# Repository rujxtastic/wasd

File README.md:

# WASD
The four most basic keys for gaming. Forward, Backward, and either Strafe or Look left/right.   
But how often do you ever step back and think, **what am I putting them through**? Your character is in a constant state of running around aimlessly, not knowing their next move. If only you could be in their shoes and empathise with them. That is the real-world problem that WASD solves.   
Realistically, WASD is the problem to the solution. You will find yourself chasing down your keyboard as it edges away from you, inflicting a fraction of your character's pain on you. A little toy that serves no real purpose (like us all?). The Onshape link can be found [here](https://cad.onshape.com/documents/5a513a08f5c3c2de2939b5e3/w/8555595e139211449ba911fa/e/058102c6ac5f3245f4983aa2?renderMode=0&uiState=69daf673cb233122137885a0).

# What does it do?
At the moment it can:
- Type W, A, S, D
- When W is typed, it moves forward via two wheels on the side.
- When S is typed, it moves backwards.
- A and D rotate it (omni wheels were too expensive!).

# Why does it do?
In the keyboard universe, most improvements have already been done long ago. Matrices, LEDs and stenographers have been completed a million times over: so much so that the people are becoming bored and complacent. WASD came to me when I was discussing ideas with my friends. I already wanted to make a simple WASD when I had the idea to attach wheels to it and give it movement. And this baby was born.

# PCB layout   

PCB:   
     
Schematic:   

# Model views

# BOM
﻿Item|Quantity|Total price|Link
---|---|---|---
Seeed XIAO RP2040 (Board + Loose Headers)|1|£3.90|https://thepihut.com/products/seeed-xiao-rp2040?variant=53975380263297
XIAO shipping|-|£3.50|
Motor pins|2|£0|
Cherry MX Clicky Switches|4|£2.80|https://customkeyboardsuk.co.uk/products/cherry-mx-blue-rgb-clicky-mechanical-keyboard-switch
Switches Shipping|-|£1.99|
L293D Motor Driver|1|£0.63|https://www.ebay.co.uk/itm/232393379693
L293D Shipping|-|£1.25|
PCB printing|1|£2.97|https://jlcpcb.com
3D printing |1|£4.81|https://jlc3dp.com
JLC shipping|-|£5.60|
Discount|-|-£7.41|https://jlc3dp.com
Screws: M2.5 x 7.5mm|6|£0.67|https://www.moddiy.com/products/1266/M2.5-x-7.5mm-Black-Screws-CM2.5X7.5.html
Screws Shipping|-|£7.43|
Toy Wheels (Colour B)|2|£1.52|https://www.aliexpress.com/item/1005007002405013.html
Motors|2|£2.22|https://www.aliexpress.com/item/1005010032893301.html
Motor Shipping|-|£2.91|
Wires (28G)|30cm|£1.77|https://www.ebay.co.uk/itm/301767024783
Total: |£36.56||   
   
To reduce costs, I would recommend buying locally and avoiding shipping.

# How to build
1. Solder the PCB. Do not solder the wires for the motors yet.
2. Flash the PCB with the firmware. I would recommend downloading Arduino, importing the .ino file, selecting the board and flashing it via USB.
3. Place the motors into the crevices on the sides.
4. Fit the PCB inside sitting on the screw holes. It should also block the motors from leaving.
5. Screw in the PCB: I would recommend from the bottom as the screws are slightly bigger than the space it has been given. You can also just buy smaller screws.
6. Solder the wires to the motor. Motor 1 Pin Header should connect to the left motor and Motor 2 Pin Header to the right. Attach the positive end to the positive side and vice versa.
7. Attach the key buttons to the button switches. This shouldn't require specialised tools.
8. Screw in the roof.
9. Attach googly eyes on the front. Their placement isn't important but without them the WASD cannot acknowledge its existence.
10. Name it! I am naming mine Jeremy.
11. Attach the wheels to the axles the motors produced.

# How to use
Simply plug it into your computer via USB-C and move around!

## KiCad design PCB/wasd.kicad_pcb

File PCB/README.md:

# PCB
This is where all the PCB parts go.

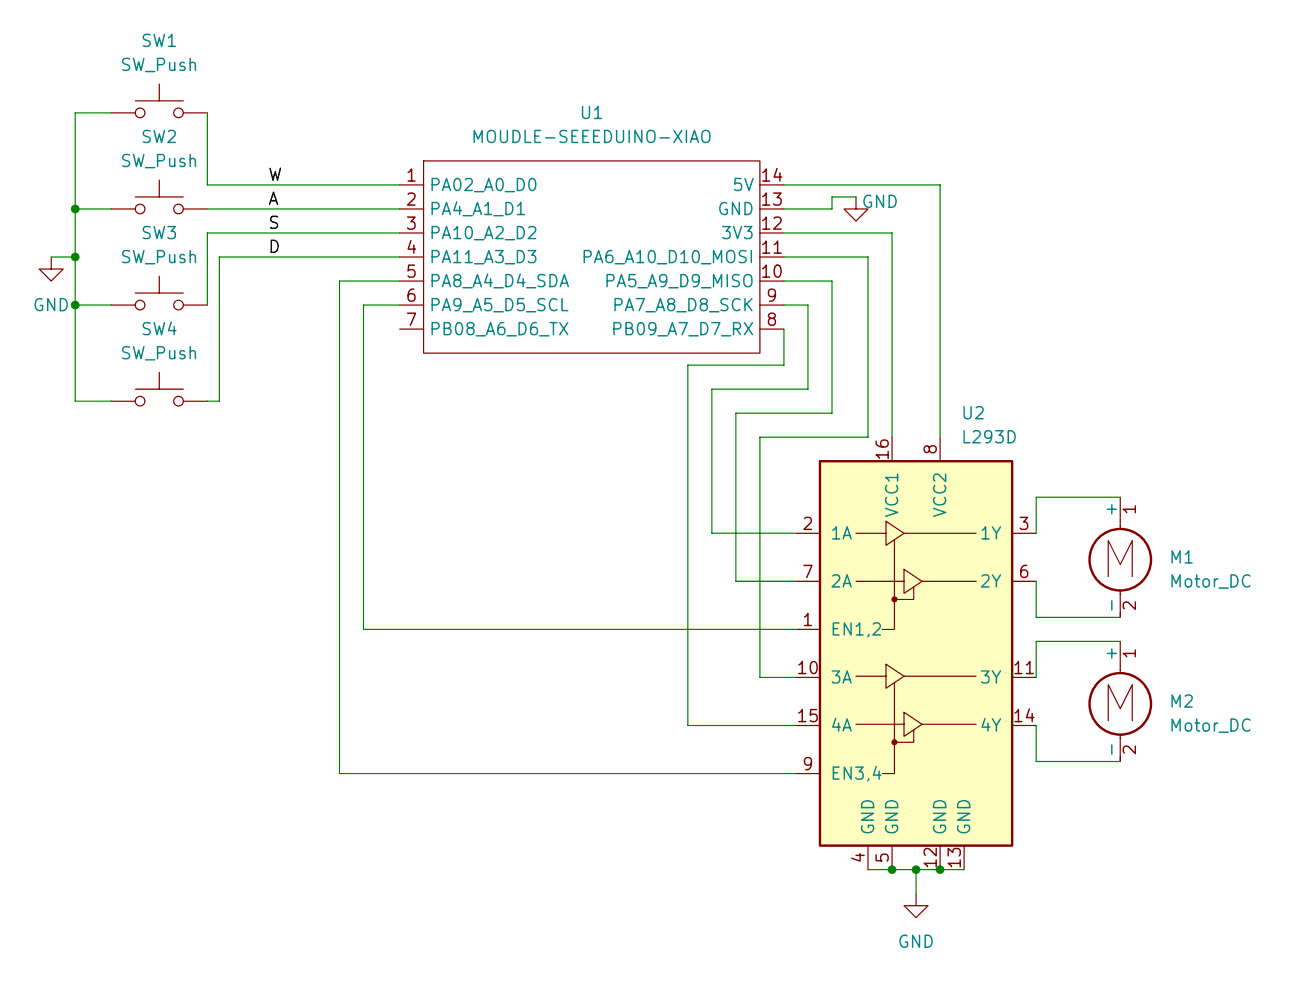
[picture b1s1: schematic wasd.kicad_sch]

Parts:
M1, M2: Motor_DC; PinHeader_1x02_P2.54mm_Vertical
SW1, SW2, SW3, SW4: SW_Push; SW_Cherry_MX_1.00u_PCB
U1: MOUDLE-SEEEDUINO-XIAO; XIAO-Generic-Hybrid-14P-2.54-21X17.8MM
U2: L293D; DIP-16_W7.62mm

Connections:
GND: SW1.1, SW2.1, SW3.1, SW4.1, U1.13 (GND), U2.4 (GND), U2.5 (GND), U2.12 (GND), U2.13 (GND)
unnamed: M1.1 (+), U2.3 (1Y)
unnamed: M1.2 (-), U2.6 (2Y)
unnamed: M2.1 (+), U2.11 (3Y)
unnamed: M2.2 (-), U2.14 (4Y)
unnamed: U1.12 (3V3), U2.16 (VCC1)
unnamed: U1.14 (5V), U2.8 (VCC2)
unnamed: SW1.2, U1.1 (PA02_A0_D0)
unnamed: SW2.2, U1.2 (PA4_A1_D1)
unnamed: U1.10 (PA5_A9_D9_MISO), U2.7 (2A)
unnamed: U1.11 (PA6_A10_D10_MOSI), U2.10 (3A)
unnamed: U1.9 (PA7_A8_D8_SCK), U2.2 (1A)
unnamed: U1.5 (PA8_A4_D4_SDA), U2.9 (EN3,4)
unnamed: U1.6 (PA9_A5_D5_SCL), U2.1 (EN1,2)
unnamed: SW3.2, U1.3 (PA10_A2_D2)
unnamed: SW4.2, U1.4 (PA11_A3_D3)
unnamed: U1.8 (PB09_A7_D7_RX), U2.15 (4A)

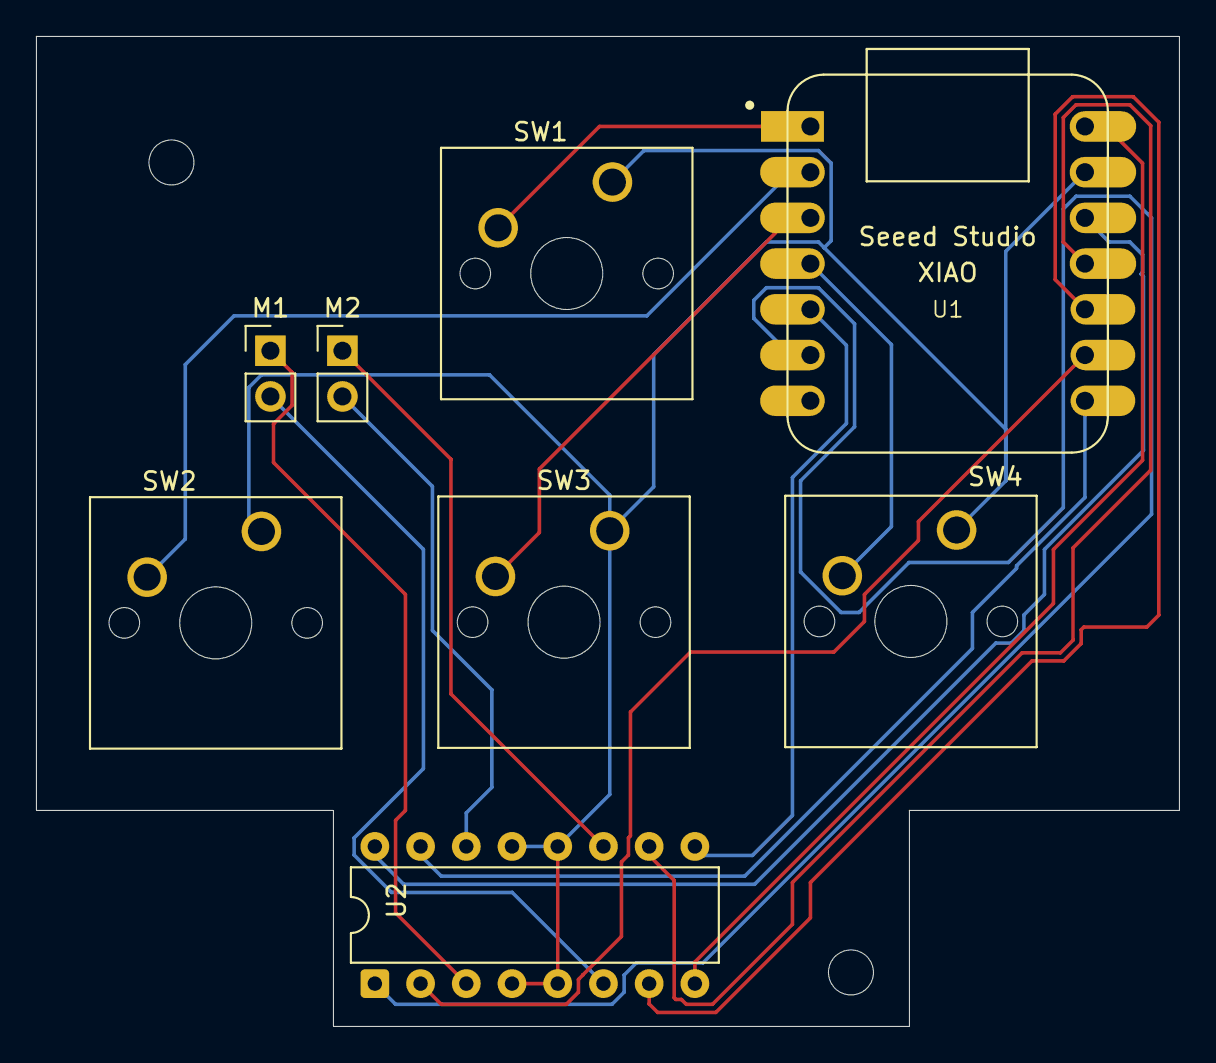
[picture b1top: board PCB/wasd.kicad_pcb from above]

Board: 2 copper layers, 63.5 x 55.0 mm, 8 parts (0 on the bottom side), 17 nets.

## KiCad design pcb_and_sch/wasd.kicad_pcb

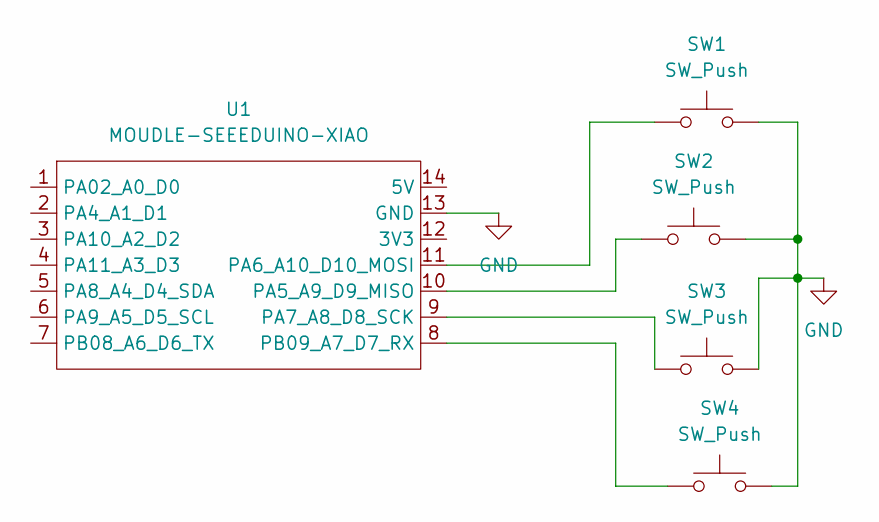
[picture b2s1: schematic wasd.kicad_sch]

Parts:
SW1, SW2, SW3, SW4: SW_Push; SW_Cherry_MX_1.00u_PCB
U1: MOUDLE-SEEEDUINO-XIAO; XIAO-Generic-Hybrid-14P-2.54-21X17.8MM

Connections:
GND: SW1.2, SW2.2, SW3.2, SW4.2, U1.13 (GND)
unnamed: SW2.1, U1.10 (PA5_A9_D9_MISO)
unnamed: SW1.1, U1.11 (PA6_A10_D10_MOSI)
unnamed: SW3.1, U1.9 (PA7_A8_D8_SCK)
unnamed: SW4.1, U1.8 (PB09_A7_D7_RX)

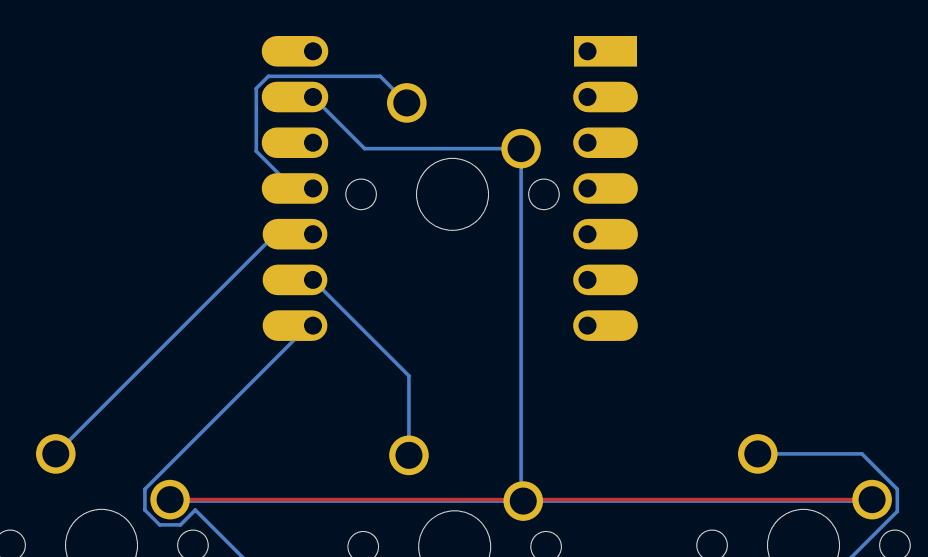
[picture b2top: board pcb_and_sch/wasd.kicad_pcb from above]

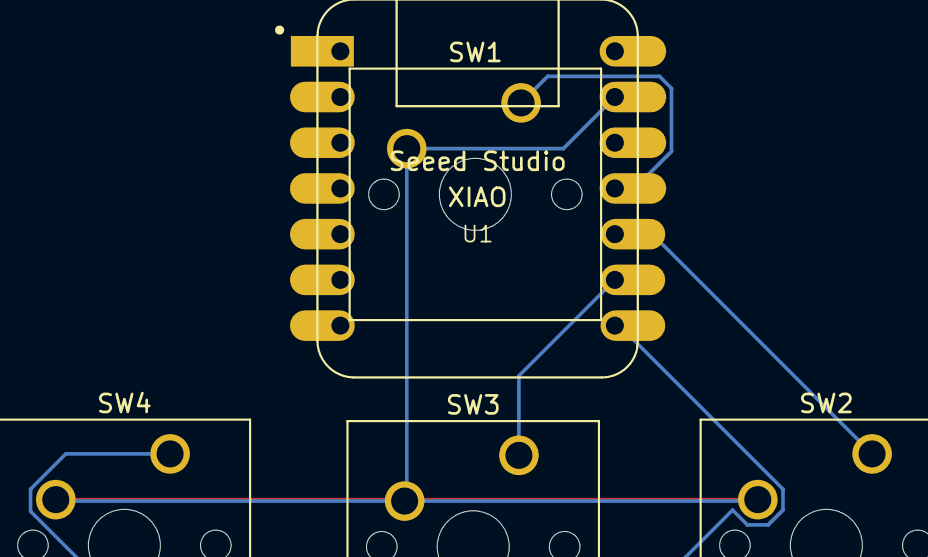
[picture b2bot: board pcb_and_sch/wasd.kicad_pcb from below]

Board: 2 copper layers, 5 parts (5 on the bottom side), 5 nets.

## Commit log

2026-03-22 Create hello
2026-03-22 Added files via upload
2026-03-22 uploaded files
2026-03-22 added keymap i guess
2026-03-22 added bottom (holding box) and top (lid) files
2026-03-22 the compiled file
2026-03-22 renamed to pcb
2026-03-22 renamed to production
2026-03-22 Create h
2026-03-22 added pcb files
2026-03-22 added top and bottom cads
2026-03-22 Create v
2026-03-22 uploaded the thing
2026-03-22 in the middle of README.md
2026-06-24 Rename WASD(2).png to zine.png
2026-06-25 Rename Assembly 1.step to Full.step
